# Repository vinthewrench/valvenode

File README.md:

# ValveNode

ValveNode is a wired field-bus irrigation valve-control system for my Raspberry Pi farm automation stack.

This project is a continuation of the work described in [Off-Grid Farm Automation with Raspberry Pi](https://www.vinthewrench.com/p/off-grid-farm-automation-raspberry-pi).

The irrigation side started with a Raspberry Pi, relay outputs, and conventional sprinkler valve wiring, described in [Raspberry Pi Internet of Things - part 2: Controlling the Irrigation valves](https://www.vinthewrench.com/p/raspberry-pi-internet-of-things-part-23c). That proved the basic idea: local software can control real irrigation hardware without a cloud service or proprietary controller. It also exposed the usual field problems: long wire runs, voltage drop, power loss, serviceability, and too many individual valve wires returning to one box.

I later experimented with more efficient solenoid drive hardware using a DRV103 in [Not Another Sprinkler Valve Article](https://www.vinthewrench.com/p/not-another-sprinkler-valve-article). That design gives a conventional valve a strong opening pulse and then reduces average power with PWM, which matters for long wire runs and battery-backed operation.

As the farm kept expanding, the wiring problem started to matter more than the valve-control problem. Every new irrigation zone meant another long wire run back to the controller, more trenching, more splices, more voltage drop, and more things to troubleshoot later. At that point, spending a few extra dollars per valve for latching solenoids was worth it if it let the field wiring become a simple 4-wire RS-485 network.

ValveNode takes the next step: instead of pulling every valve wire back to the controller, it moves small controller cards out into the field.

A Raspberry Pi talks to a Valve Master over I2C. The Valve Master starts a 4-wire RS-485 field cable carrying power and data. Valve Node cards sit along that cable, and each card drives a local latching irrigation solenoid with a short polarity-controlled pulse.

The goal is simple: irrigation control that is local, wired, understandable, repairable, and expandable.

## Overview

The project has two primary components:

- `valvenode-master`  
  ATmega88PB-based I2C-to-RS-485 master controller.

- `valvenode-slave`  
  ATtiny4313-based RS-485 valve node for controlling latching irrigation valves.

The upstream controller talks to the Valve Master over I2C. The Valve Master controls field power and communicates with downstream Valve Nodes over RS-485.

### Latching Solenoids

ValveNode is designed around low-voltage DC latching irrigation solenoids. The initial supported solenoids are:

| Manufacturer | Part | Description | Notes |
|---|---:|---|---|
| Hunter | [458200](https://www.hunterirrigation.com/irrigation-product/solenoids/458200) | DC latching solenoid | Common Hunter solenoid for battery-operated and DC-latching valve control |
| Rain Bird | [K80920](https://store.rainbird.com/tbospsol-tbos-potted-latching-solenoid.html) / TBOSPSOL | 9 V DC potted latching solenoid | Fits many Rain Bird valve bodies, including DV, DVF, ASVF, PGA, PEB, PESB, GB, EFB-CP, BPE, and BPES series valves |

A latching solenoid is not powered continuously. The Valve Node drives it with a short polarity-controlled pulse through the H-bridge: one polarity opens the valve, the opposite polarity closes it, and then the output is turned off.

## Project Goals

- Wired field-bus control for irrigation valves
- No cloud dependency
- No wireless dependency
- Local 12 V field-power switching
- Half-duplex RS-485 node communication
- AVR-based firmware that can be understood, built, and serviced
- KiCad hardware source included
- Separate master firmware, simulator, Linux test tool, and node firmware

## Repository Layout

~~~text
valvenode/
├── valvenode-master/
│   ├── docs/
│   ├── firmware/
│   ├── hw/
│   │   └── 1.0/
│   ├── sim/
│   └── test/
└── valvenode-slave/
    ├── docs/
    ├── firmware/
    ├── hw/
    │   ├── 1.0/
    │   └── 1.1/
    └── test/
~~~

## Valve Master

Path:

~~~text
valvenode-master/
~~~

The Valve Master is the central controller for the valve-node network.

It performs these jobs:

- Accepts host commands over I2C
- Controls switched 12 V field-bus power
- Sends RS-485 commands to downstream valve nodes
- Receives valve-node replies
- Maintains node discovery state
- Reports status and command results to the host
- Provides local visual status indication
- Exposes AVR ISP programming access

Default I2C address:

~~~text
0x09
~~~

Address `0x08` is reserved for a separate power-control board, so `0x09` is used as the default Valve Master address.

### Valve Master Hardware

Path:

~~~text
valvenode-master/hw/1.0/
~~~

Important KiCad source files:

~~~text
valvenode-master.kicad_pro
valvenode-master.kicad_sch
valvenode-master.kicad_pcb
~~~

The master board uses:

- ATmega88PB-AU
- MAX485-style RS-485 transceiver
- Relay-switched 12 V field-bus output
- FAULT input
- COMM and FAULT indicators
- AVR ISP header
- I2C host-side interface

### Valve Master Firmware

Path:

~~~text
valvenode-master/firmware/
~~~

Files:

~~~text
makefile
valvenode_master.c
~~~

The firmware implements the production Valve Master behavior:

- I2C slave interface
- Register map
- Deferred command handling
- RS-485 transmit/receive control
- Field-bus power control
- Node discovery
- Valve-node command dispatch
- Result and reply registers
- Fault/status reporting

Directed RS-485 commands include timeout handling and retry behavior. A single missed node reply should not turn into an immediate hard failure on a slow irrigation field bus.

Build:

~~~bash
cd valvenode-master/firmware
make
~~~

### Valve Master Simulator

Path:

~~~text
valvenode-master/sim/
~~~

Files:

~~~text
makefile
valvenode_master_sim.c
~~~

The simulator models the master command/register behavior for bench testing without hardware.

Build:

~~~bash
cd valvenode-master/sim
make
~~~

### Valve Master Linux Test Tool

Path:

~~~text
valvenode-master/test/
~~~

Files:

~~~text
makefile
Doxyfile
src/
~~~

Source files:

~~~text
I2C.cpp
I2C.hpp
LogMgr.cpp
LogMgr.hpp
TimeStamp.cpp
TimeStamp.hpp
Valve_master.cpp
Valve_master.hpp
main.cpp
~~~

The test tool is a Linux-side C++ program used to talk to the Valve Master over `/dev/i2c-*`.

The main C++ class is:

~~~text
Valve_master
~~~

It wraps the Valve Master I2C register map and command model.

Typical responsibilities:

- Open the Linux I2C device
- Select the Valve Master I2C address
- Read and write registers
- Submit commands
- Wait for command completion
- Read command results
- Read reply registers
- Read discovered node map
- Query firmware versions
- Control field power
- Ping nodes
- Set valve/channel state

Build:

~~~bash
cd valvenode-master/test
make
~~~

Common `valve` commands:

~~~bash
./valve status
./valve power on
./valve power off
./valve who
./valve map
./valve ping 1
./valve set 1 1 on
./valve set 1 1 off
./valve channel 1 1 status
./valve version master
./valve version 1
./valve identify 1
./valve cancel
~~~

Provisioning commands:

~~~bash
./valve config
./valve assign 7
./valve move 7 8
~~~

### Hammer Test

Path:

~~~text
valvenode-master/test/hammer.sh
~~~

`hammer.sh` repeatedly exercises the full Valve Master path.

Test pattern:

~~~text
power on
ping nodes
initial status nodes
loop:
  set ON nodes
  status nodes
  set OFF nodes
  status nodes
final status nodes
power off
~~~

Example:

~~~bash
cd valvenode-master/test
./hammer.sh 25
NODES="1 3 4 5 6" CHANNEL=1 ./hammer.sh 500
~~~

Optional settings:

~~~bash
CHANNEL=2 ./hammer.sh 25
VERBOSE=1 ./hammer.sh 25
VALVE_BIN=./valve ./hammer.sh 25
NODES="1 3 4 5 6" ./hammer.sh 25
RETRY_ON_FAIL=1 ./hammer.sh 25
~~~

Recent bench result:

~~~text
500 loops
5 nodes tested: 1 3 4 5 6
channel 1
10,016 commands
0 failures
100% first-try pass rate
~~~

Generate local Doxygen docs:

~~~bash
cd valvenode-master/test
doxygen Doxyfile
open docs/html/index.html
~~~

## Valve Master I2C Register Model

The host talks to the master through a small register map.

Important registers include:

~~~text
REG_COMMAND
REG_STATUS
REG_ARG0
REG_ARG1
REG_ARG2
REG_RESULT
REG_POWER_STATE
REG_NODE_COUNT
REG_REPLY_NODE
REG_REPLY_CMD
REG_REPLY_ARG0
REG_REPLY_ARG1
REG_VERSION_HI
REG_VERSION_LO
REG_NODE_MAP
~~~

Important command values include:

~~~text
CMD_POWER_ON
CMD_POWER_OFF
CMD_WHO
CMD_PING
CMD_SET_CHANNEL
CMD_GET_CHANNEL_STATUS
CMD_GET_NODE_VERSION
CMD_IDENTIFY
CMD_CANCEL
CMD_CONFIG
CMD_ASSIGN
CMD_CLEAR_ERROR
CMD_SET_ERROR
CMD_CLOSE_ALL
~~~

Important status bits include:

~~~text
STATUS_BUSY
STATUS_ERROR
STATUS_POWER_ON
~~~

Important result values include:

~~~text
RESULT_OK
RESULT_BAD_COMMAND
RESULT_BAD_NODE
RESULT_BAD_CHANNEL
RESULT_NODE_NOT_FOUND
RESULT_UNSUPPORTED_CHANNEL
RESULT_CONFIG_REQUIRED
RESULT_ADDRESS_IN_USE
RESULT_BUSY
RESULT_RS485_TIMEOUT
RESULT_RS485_BAD_CHECKSUM
RESULT_RS485_BAD_REPLY
RESULT_POWER_OFF
~~~

## Valve Node

Path:

~~~text
valvenode-slave/
~~~

The Valve Node is the remote field device. It receives RS-485 commands and drives a 12 V latching irrigation valve.

Core functions:

- Receive framed RS-485 commands
- Check destination address
- Respond to discovery and status commands
- Drive a latching valve using a polarity-controlled pulse
- Turn the H-bridge fully off after each pulse
- Report current logical valve state

### Valve Node Hardware

Paths:

~~~text
valvenode-slave/hw/1.0/
valvenode-slave/hw/1.1/
~~~

Important KiCad source files:

~~~text
valvenode.kicad_pro
valvenode.kicad_sch
valvenode.kicad_pcb
~~~

The `1.1` hardware directory is the newer active revision.

The node hardware uses:

- ATtiny4313
- 5 V RS-485 transceiver
- VNH7100BAS / VNH7100BASTR H-bridge
- 12 V latching irrigation valve output
- 12 V field-bus input
- Local 5 V regulator
- Optional status LED

Basic field connection:

~~~text
+12 V
GND
RS-485 A
RS-485 B
~~~

The design is intended for direct-burial irrigation cable.

Recommended cable:

- 18/4 acceptable for shorter runs
- 16/4 preferred for longer runs or higher node counts

### Valve Node Power Architecture

The node receives 12 V from the field cable.

Power paths:

- 12 V directly feeds the valve driver supply
- 12 V feeds a local 5 V regulator
- 5 V powers the ATtiny4313 and RS-485 transceiver

Recommended protection and stability parts include:

- Bidirectional TVS across the 12 V input
- Bulk capacitance near the H-bridge supply
- 0.1 uF local decoupling at MCU and transceiver
- Additional 5 V bulk capacitance near the MCU
- Reverse-polarity protection where practical

For master-side field power switching, allow roughly 250 to 300 ms after switching on the 12 V field bus before sending node commands.

### Valve Node Firmware

Path:

~~~text
valvenode-slave/firmware/
~~~

Files:

~~~text
makefile
valvenode.c
valvenode_example_commands.txt
~~~

The firmware target is the ATtiny4313.

Firmware responsibilities:

- UART receive
- RS-485 command parsing
- Address matching
- Optional checksum checking
- Valve open pulse
- Valve close pulse
- Status reporting
- Ping reply
- WHO discovery reply
- Safe H-bridge shutdown after each pulse

Build:

~~~bash
cd valvenode-slave/firmware
make
~~~

### Valve Node Test Tool

Path:

~~~text
valvenode-slave/test/
~~~

Files:

~~~text
makefile
src/main.cpp
~~~

The `vnode` utility is used for direct bench testing of valve nodes over a serial port. It assumes the computer is connected to the RS-485 bus through a USB-to-RS-485 adapter.

This bypasses the Valve Master and talks directly to the nodes.

Build:

~~~bash
cd valvenode-slave/test
make
~~~

Example:

~~~bash
./vnode -d /dev/ttyUSB0 who
./vnode -d /dev/ttyUSB0 ping 1
./vnode -d /dev/ttyUSB0 open 1 1
./vnode -d /dev/ttyUSB0 close 1 1
~~~

Typical output:

~~~text
$ ./vnode -d /dev/ttyUSB0 who
device: /dev/ttyUSB0
baud:   9600
tx: :FFW\r
rx: :01WB8  [checksum ok] node=1 WHO
rx: :02WB9  [checksum ok] node=2 WHO
~~~

`vnode` can also be used to configure a fresh node, assign its address, and verify that it answers before it goes into the field.

## RS-485 Valve Node Protocol

The Valve Master and Valve Nodes communicate over a half-duplex RS-485 bus.

The node protocol is command/response. The master sends a framed command. A node replies only when addressed or when participating in a controlled discovery response.

Typical commands:

~~~text
PING
STATUS
OPEN
CLOSE
WHO
IDENTIFY
CONFIG
ASSIGN
VERSION
~~~

Typical behavior:

- `PING` confirms node presence
- `STATUS` reports logical valve/channel state
- `OPEN` sends the open-polarity valve pulse
- `CLOSE` sends the close-polarity valve pulse
- `WHO` is used for node discovery
- `IDENTIFY` asks a node to identify itself
- `CONFIG` enters configuration behavior
- `ASSIGN` sets or changes a node address
- `VERSION` reports firmware version

Broadcast state-changing commands should be avoided unless explicitly implemented and safe.

## Useful Linux I2C Commands

List I2C buses:

~~~bash
i2cdetect -l
ls -l /dev/i2c-*
~~~

Scan I2C bus 1:

~~~bash
i2cdetect -y 1
~~~

Look for the Valve Master at address `0x09`.

Check user permissions for I2C:

~~~bash
groups
ls -l /dev/i2c-*
~~~

If needed, add the user to the `i2c` group on Linux:

~~~bash
sudo usermod -aG i2c $USER
~~~

Then log out and back in.

## Development Notes

- The Valve Master default I2C address is `0x09`.
- The Valve Master controls field-bus 12 V power.
- The Valve Nodes are not autonomous irrigation controllers.
- Valve Nodes execute direct command/response behavior.
- Latching valves must be driven with short pulses, not continuous power.
- H-bridge outputs must be turned off after each pulse.
- RS-485 bus direction control must be handled carefully to avoid bus contention.
- Field wiring should assume noise, voltage drop, wet boxes, lightning exposure, and field-service abuse.

## Current Project Status

The repository currently contains:

- Valve Master hardware design
- Valve Master firmware
- Valve Master simulator
- Valve Master Linux I2C test tool: `valve`
- Valve Master hammer test: `hammer.sh`
- Valve Node hardware revisions
- Valve Node firmware
- Valve Node direct RS-485 test tool: `vnode`
- Protocol and design documentation

Current bench status:

- Valve Master can switch field power
- Valve Master can communicate with multiple valve nodes over RS-485
- Valve nodes respond to discovery, ping, set, and status commands
- `hammer.sh` has completed a 500-loop, 10,016-command bench test across five nodes with zero failures

Remaining validation:

- Confirm final latching-solenoid open/close polarity with real valve bodies
- Test final assembled boards in outdoor enclosures
- Validate longer real field-cable runs
- Continue field reliability testing before treating the system as deployed infrastructure

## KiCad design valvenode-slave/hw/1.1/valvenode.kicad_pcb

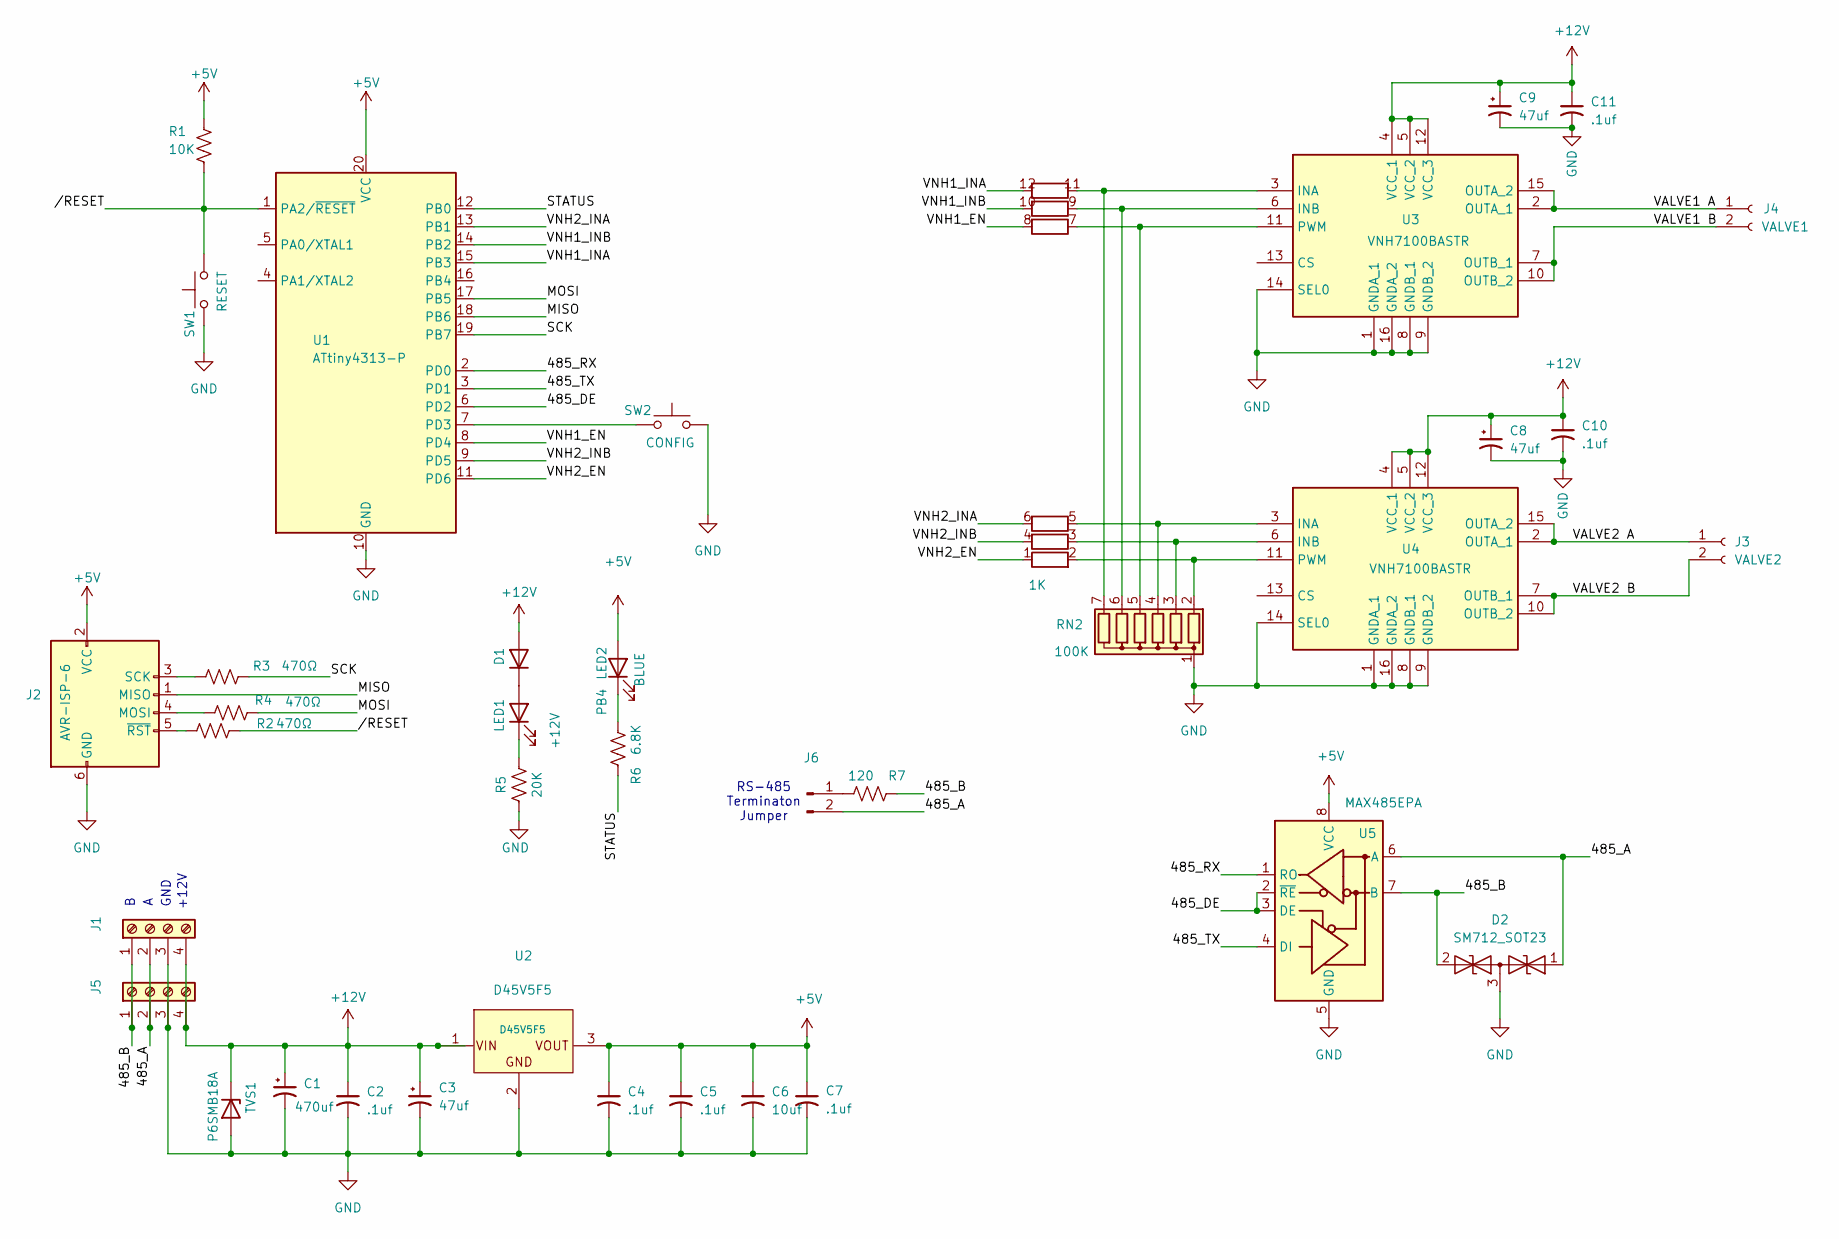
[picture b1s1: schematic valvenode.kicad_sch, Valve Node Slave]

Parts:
C1: 470uf; CP_Radial_D5.0mm_P2.00mm
C2, C4, C5, C7, C10, C11: .1uf; RCER71H104K0DBH03A
C3, C8, C9: 47uf; CP_Radial_D5.0mm_P2.00mm
C6: 10uf; CP_Radial_D5.0mm_P2.00mm
D1: 1N4148WS; D_DO-35_SOD27_P7.62mm_Horizontal
D2: SM712_SOT23; SOT-23
J1, J5: +12; TerminalBlock_Phoenix_MKDS-1,5-4-5.08_1x04_P5.08mm_Horizont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
J2: AVR-ISP-6; PinHeader_2x03_P2.54mm_Vertical
J3: VALVE2; TerminalBlock_Phoenix_MKDS-1,5-2-5.08_1x02_P5.08mm_Horizont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
J4: VALVE1; TerminalBlock_Phoenix_MKDS-1,5-2-5.08_1x02_P5.08mm_Horizont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
J6: Conn_01x02_Pin; PinHeader_1x02_P2.54mm_Vertical
LED1: 151033GS03000; LED_D3.0mm
LED2: 1510x4BS03000; LED_D3.0mm
R1: 10K; R_Axial_DIN0204_L3.6mm_D1.6mm_P7.62mm_Horizontal
R2, R3, R4: 470Ω; R_Axial_DIN0204_L3.6mm_D1.6mm_P7.62mm_Horizontal
R5: 20K; R_Axial_DIN0204_L3.6mm_D1.6mm_P7.62mm_Horizontal
R6: 6.8K; R_Axial_DIN0204_L3.6mm_D1.6mm_P7.62mm_Horizontal
R7: 120; R_Axial_DIN0204_L3.6mm_D1.6mm_P7.62mm_Horizontal
RN1: 1K; R_Array_SIP12; Manufacturer_Part_Number 4612X-102-102LF
RN2: 100K; R_Array_SIP7; Manufacturer_Part_Number 4607X-101-104LF
SW1: RESET; SW_PUSH_6mm
SW2: CONFIG; SW_PUSH_6mm
TVS1: P6SMB18A; D_SMB_Handsoldering
U1: ATtiny4313-P; DIP-20_W7.62mm
U2: D45V5F5
U3, U4: VNH7100BASTR; SOIC127P600X175-16N; Manufacturer_Part_Number VNH7100BASTR; Mouser Part Number 511-VNH7100BASTR
U5: MAX485EPA; DIP-8_W7.62mm

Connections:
+5V: C4.1, C5.1, C6.1, C7.1, J2.2 (VCC), LED2.2 (A), R1.1, U1.20 (VCC), U2.3 (VOUT), U5.8 (VCC)
+12V: C1.1, C2.1, C3.1, C8.1, C9.1, C10.1, C11.1, D1.2 (A), J1.4, J5.4, TVS1.1 (K), U2.1 (VIN), U3.4 (VCC_1), U3.5 (VCC_2), U3.12 (VCC_3), U4.4 (VCC_1), U4.5 (VCC_2), U4.12 (VCC_3)
/485_A: D2.1 (A1), J1.2, J5.2, J6.2, U5.6 (A)
/485_B: D2.2 (A2), J1.1, J5.1, R7.1, U5.7 (B)
/485_DE: U1.6 (PD2), U5.2 (~RE), U5.3 (DE)
/485_RX: U1.2 (PD0), U5.1 (RO)
/485_TX: U1.3 (PD1), U5.4 (DI)
/MISO: J2.1 (MISO), U1.18 (PB6)
/MOSI: R4.1, U1.17 (PB5)
/SCK: R3.1, U1.19 (PB7)
/STATUS: R6.1, U1.12 (PB0)
/VALVE1 A: J4.1, U3.2 (OUTA_1), U3.15 (OUTA_2)
/VALVE1 B: J4.2, U3.7 (OUTB_1), U3.10 (OUTB_2)
/VALVE2 A: J3.1, U4.2 (OUTA_1), U4.15 (OUTA_2)
/VALVE2 B: J3.2, U4.7 (OUTB_1), U4.10 (OUTB_2)
/VNH1_EN: RN1.8 (R4.2), U1.8 (PD4)
/VNH1_INA: RN1.12 (R6.2), U1.15 (PB3)
/VNH1_INB: RN1.10 (R5.2), U1.14 (PB2)
/VNH2_EN: RN1.1 (R1.1), U1.11 (PD6)
/VNH2_INA: RN1.6 (R3.2), U1.13 (PB1)
/VNH2_INB: RN1.4 (R2.2), U1.9 (PD5)
//RESET: R1.2, R2.1, SW1.2, U1.1 (PA2/~RESET)
GND: C1.2, C2.2, C3.2, C4.2, C5.2, C6.2, C7.2, C8.2, C9.2, C10.2, C11.2, D2.3 (common), J1.3, J2.6 (GND), J5.3, R5.2, RN2.1 (common), SW1.1, SW2.2, TVS1.2 (A), U1.10 (GND), U2.2 (GND), U3.1 (GNDA_1), U3.8 (GNDB_1), U3.9 (GNDB_2), U3.14 (SEL0), U3.16 (GNDA_2), U4.1 (GNDA_1), U4.8 (GNDB_1), U4.9 (GNDB_2), U4.14 (SEL0), U4.16 (GNDA_2), U5.5 (GND)
unnamed: D1.1 (K), LED1.2 (A)
unnamed: J2.4 (MOSI), R4.2
unnamed: J2.3 (SCK), R3.2
unnamed: J2.5 (~RST), R2.2
unnamed: J6.1, R7.2
unnamed: LED1.1 (K), R5.1
unnamed: LED2.1 (K), R6.2
unnamed: RN1.2 (R1.2), RN2.2 (R1), U4.11 (PWM)
unnamed: RN1.3 (R2.1), RN2.3 (R2), U4.6 (INB)
unnamed: RN1.5 (R3.1), RN2.4 (R3), U4.3 (INA)
unnamed: RN1.7 (R4.1), RN2.5 (R4), U3.11 (PWM)
unnamed: RN1.9 (R5.1), RN2.6 (R5), U3.6 (INB)
unnamed: RN1.11 (R6.1), RN2.7 (R6), U3.3 (INA)
unnamed: SW2.1, U1.7 (PD3)

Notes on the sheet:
RS-485 Terminaton Jumper
GND
+12V

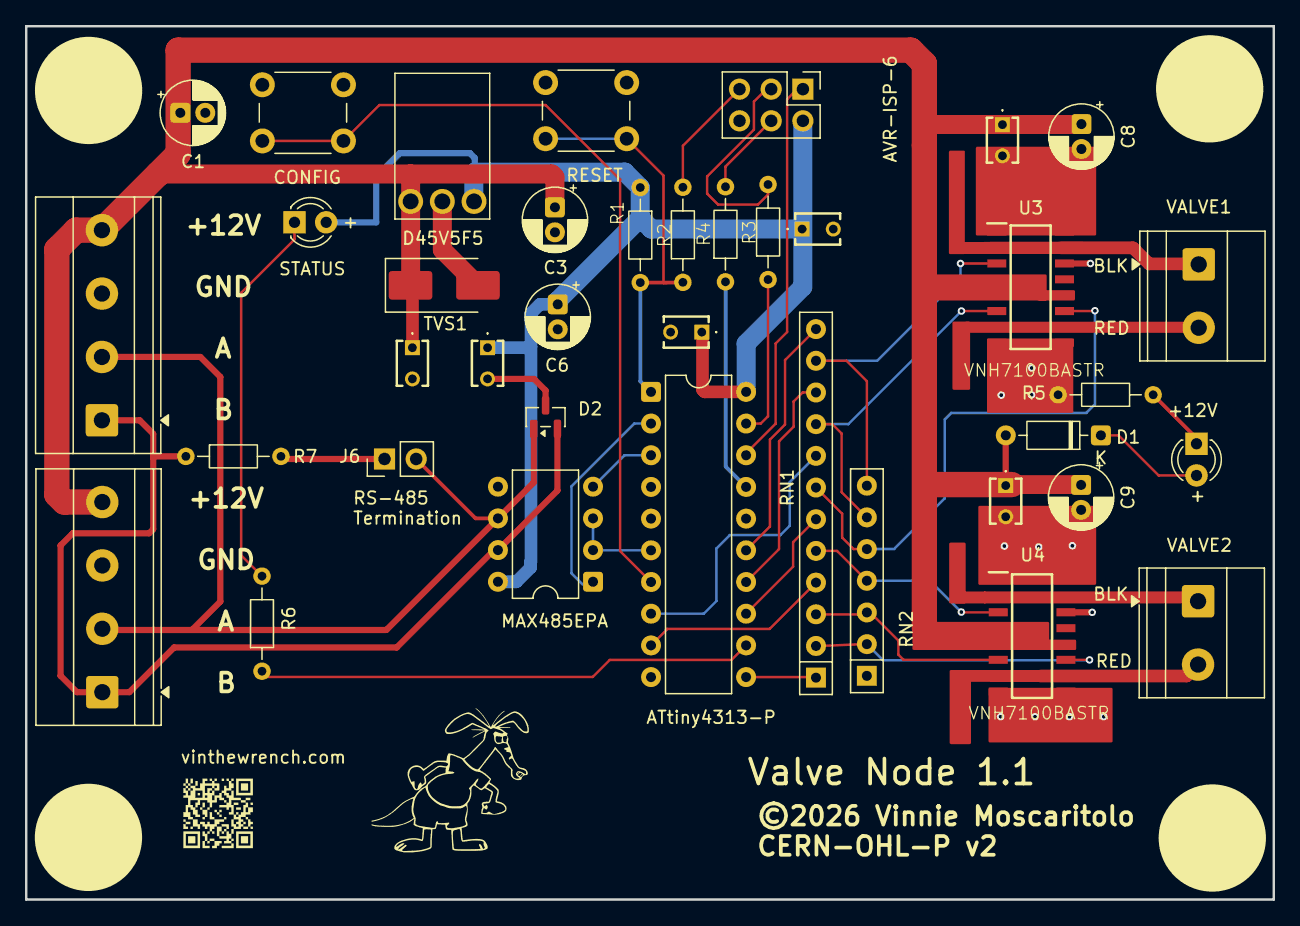
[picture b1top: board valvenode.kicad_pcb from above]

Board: 2 copper layers, 100.0 x 70.0 mm, 39 parts (0 on the bottom side), 37 nets.

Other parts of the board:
X: LOGO; aard1

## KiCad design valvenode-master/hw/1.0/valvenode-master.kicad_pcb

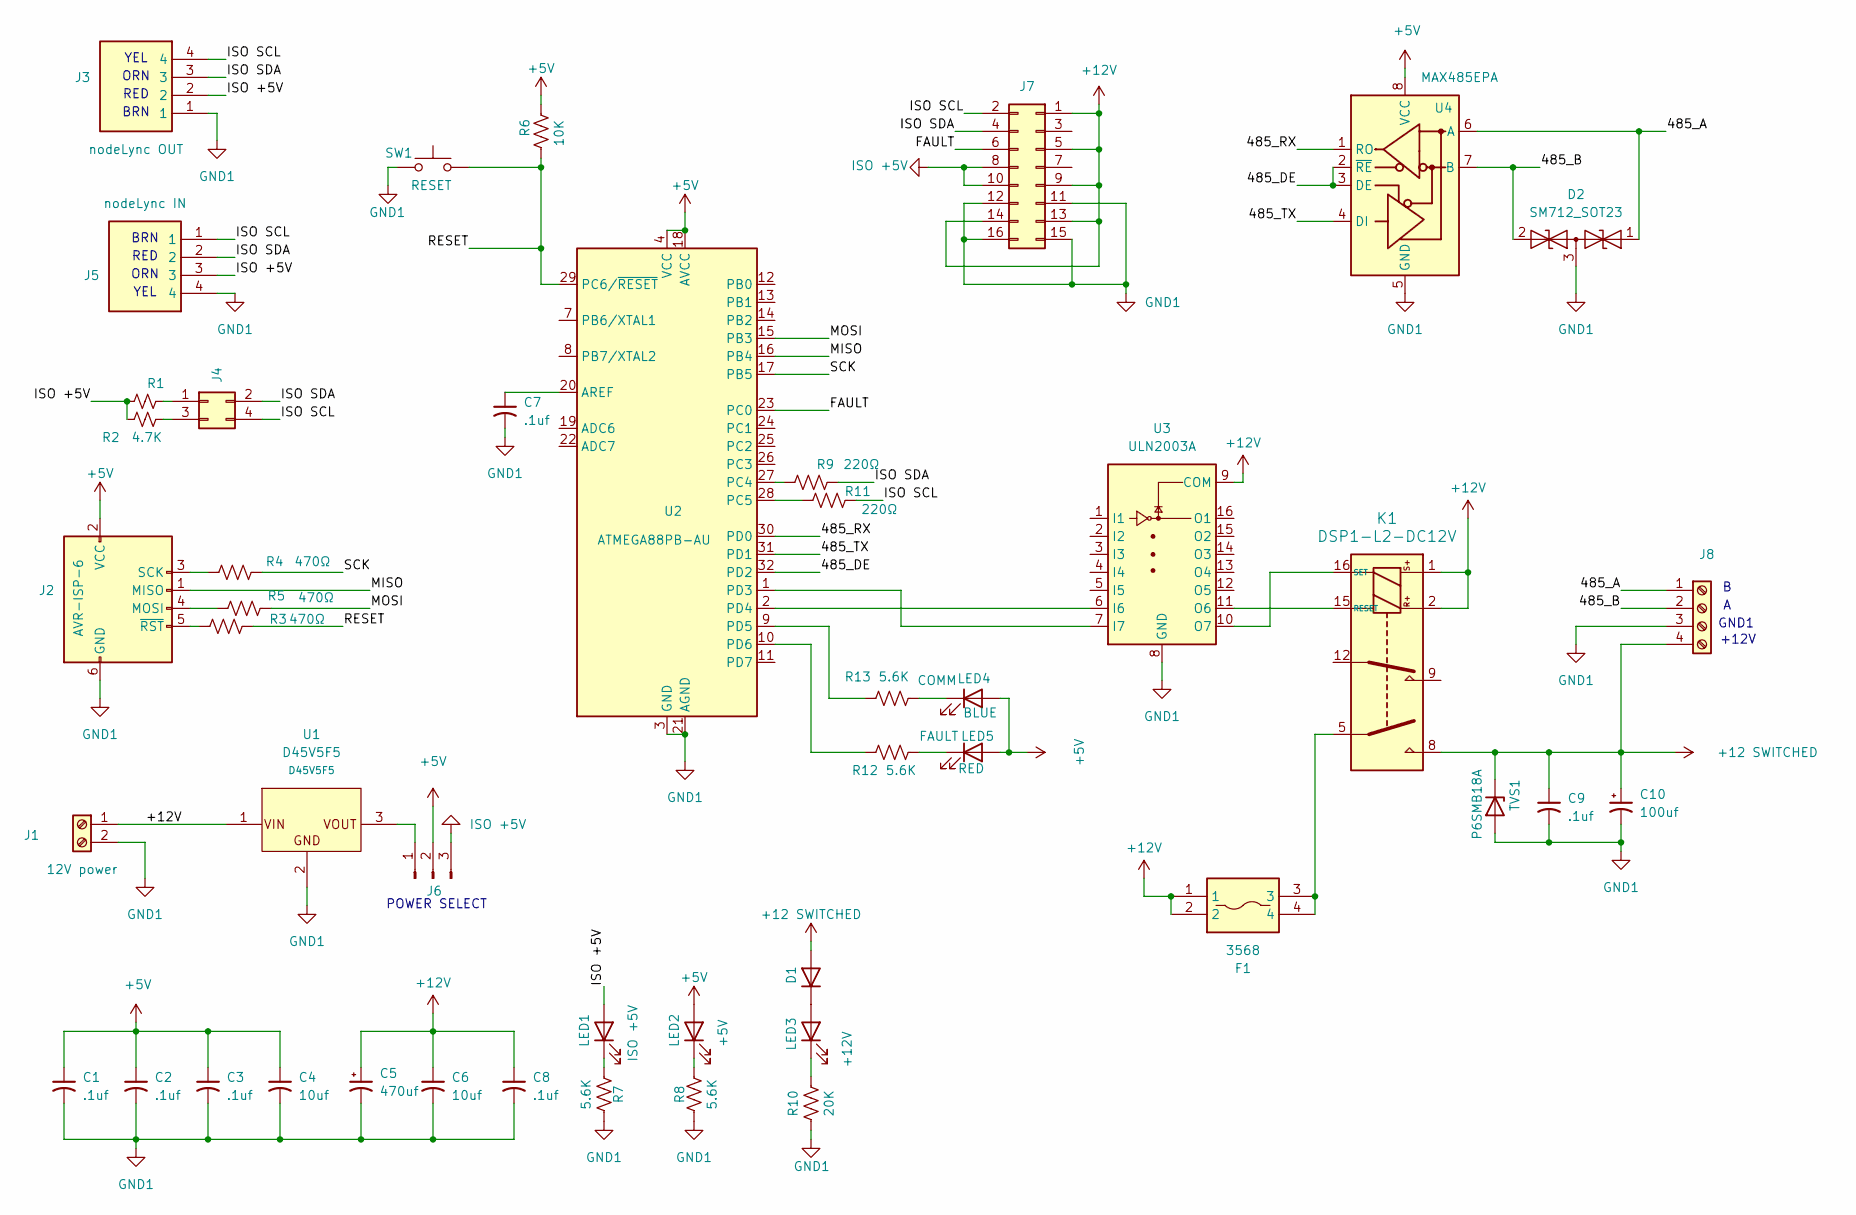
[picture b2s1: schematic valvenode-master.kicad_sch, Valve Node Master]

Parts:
C1, C2, C3, C7, C8, C9: .1uf; RCER71H104K0DBH03A
C4, C6: 10uf; CP_Radial_D5.0mm_P2.00mm
C5: 470uf; CP_Radial_D8.0mm_P3.50mm
C10: 100uf; CP_Radial_D8.0mm_P3.50mm
D1: 1N4148WS; D_DO-35_SOD27_P7.62mm_Horizontal
D2: SM712_SOT23; SOT-23
F1: 3568; Mouser Part Number 534-3568
J1: 12V power; TerminalBlock_Phoenix_MKDS-1,5-2-5.08_1x02_P5.08mm_Horizont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
J2: AVR-ISP-6; PinHeader_2x03_P2.54mm_Vertical
J3, J5: 70551-0003; 705510003; Manufacturer_Part_Number 70551-0003; Mouser Part Number 538-70551-0003
J4: Conn_02x02_Odd_Even; PinHeader_2x02_P2.54mm_Vertical
J6: Conn_01x03_Pin; PinHeader_1x03_P2.54mm_Vertical
J7: Conn_02x08_Odd_Even; PinSocket_2x08_P2.54mm_Vertical
J8: +12; TerminalBlock_Phoenix_MKDS-1,5-4-5.08_1x04_P5.08mm_Horizont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
K1: DSP1-L2-DC12V
LED1, LED2, LED3: 151033GS03000; LED_D3.0mm
LED4: 151034BS03000; LED_D3.0mm
LED5: 151033RS03000; LED_D3.0mm
R1, R2: 4.7K; R_Axial_DIN0204_L3.6mm_D1.6mm_P7.62mm_Horizontal
R3, R4, R5: 470Ω; R_Axial_DIN0204_L3.6mm_D1.6mm_P7.62mm_Horizontal
R6: 10K; R_Axial_DIN0204_L3.6mm_D1.6mm_P7.62mm_Horizontal
R7, R8, R12, R13: 5.6K; R_Axial_DIN0204_L3.6mm_D1.6mm_P7.62mm_Horizontal
R9, R11: 220Ω; R_Axial_DIN0204_L3.6mm_D1.6mm_P7.62mm_Horizontal
R10: 20K; R_Axial_DIN0204_L3.6mm_D1.6mm_P7.62mm_Horizontal
SW1: RESET; SW_PUSH_6mm
TVS1: P6SMB18A; D_SMB_Handsoldering
U1: D45V5F5
U2: ATMEGA88PB-AU; TQFP-32_7x7mm_P0.8mm
U3: ULN2003A; DIP-16_W7.62mm
U4: MAX485EPA; DIP-8_W7.62mm

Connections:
+5V: C1.1, C2.1, C3.1, C4.1, J2.2 (VCC), J6.2, LED2.2 (A), LED4.2 (A), LED5.2 (A), R6.1, U2.4 (VCC), U2.6 (VCC), U2.18 (AVCC), U4.8 (VCC); also elsewhere on the board
+12 SWITCHED: C9.1, C10.1, D1.2 (A), J8.4, K1.8, TVS1.1 (K)
+12V: C5.1, C6.1, C8.1, F1.1, F1.2, J1.1, J7.1, J7.5, J7.9, J7.13, J7.14, K1.1, K1.2, U1.1 (VIN), U3.9 (COM); also elsewhere on the board
/485_A: D2.1 (A1), J8.1, U4.6 (A)
/485_B: D2.2 (A2), J8.2, U4.7 (B)
/485_DE: U2.32 (PD2), U4.2 (~RE), U4.3 (DE)
/485_RX: U2.30 (PD0), U4.1 (RO)
/485_TX: U2.31 (PD1), U4.4 (DI)
/FAULT: J7.6, U2.23 (PC0)
/ISO SCL: J3.4, J4.4, J5.1, J7.2, R11.1
/ISO SDA: J3.3, J4.2, J5.2, J7.4, R9.1
/MISO: J2.1 (MISO), U2.16 (PB4)
/MOSI: R5.1, U2.15 (PB3)
/RESET: R3.1, R6.2, SW1.2, U2.29 (PC6/~RESET)
/SCK: R4.1, U2.17 (PB5)
GND1: C1.2, C2.2, C3.2, C4.2, C5.2, C6.2, C7.2, C8.2, C9.2, C10.2, D2.3 (common), J1.2, J2.6 (GND), J3.1, J5.4, J7.11, J7.12, J7.15, J7.16, J8.3, R7.2, R8.1, R10.2, SW1.1, TVS1.2 (A), U1.2 (GND), U2.3 (GND), U2.5 (GND), U2.21 (AGND), U3.8 (GND), U4.5 (GND)
ISO +5V: J3.2, J5.3, J6.3, J7.8, J7.10, LED1.2 (A), R1.2, R2.2
unnamed: D1.1 (K), LED3.2 (A)
unnamed 18: F1.3, F1.4, K1.5; also elsewhere on the board
unnamed: J2.4 (MOSI), R5.2
unnamed: J2.3 (SCK), R4.2
unnamed: J2.5 (~RST), R3.2
unnamed: J4.1, R1.1
unnamed: J4.3, R2.1
unnamed: J6.1, U1.3 (VOUT)
unnamed: K1.15 (RESET), U3.11 (O6)
unnamed: K1.16 (SET), U3.10 (O7)
unnamed: LED1.1 (K), R7.1
unnamed: LED2.1 (K), R8.2
unnamed: LED3.1 (K), R10.1
unnamed 30: LED4.1 (K), R13.2; also elsewhere on the board
unnamed 31: LED5.1 (K), R12.2; also elsewhere on the board
unnamed: C7.1, U2.20 (AREF)
unnamed: R9.2, U2.27 (PC4)
unnamed: R11.2, U2.28 (PC5)
unnamed: U2.1 (PD3), U3.7 (I7)
unnamed: U2.2 (PD4), U3.6 (I6)
unnamed: R13.1, U2.9 (PD5)
unnamed: R12.1, U2.10 (PD6)

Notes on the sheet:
GND1
YEL
BRN
ORN
+12V
POWER SELECT
RED

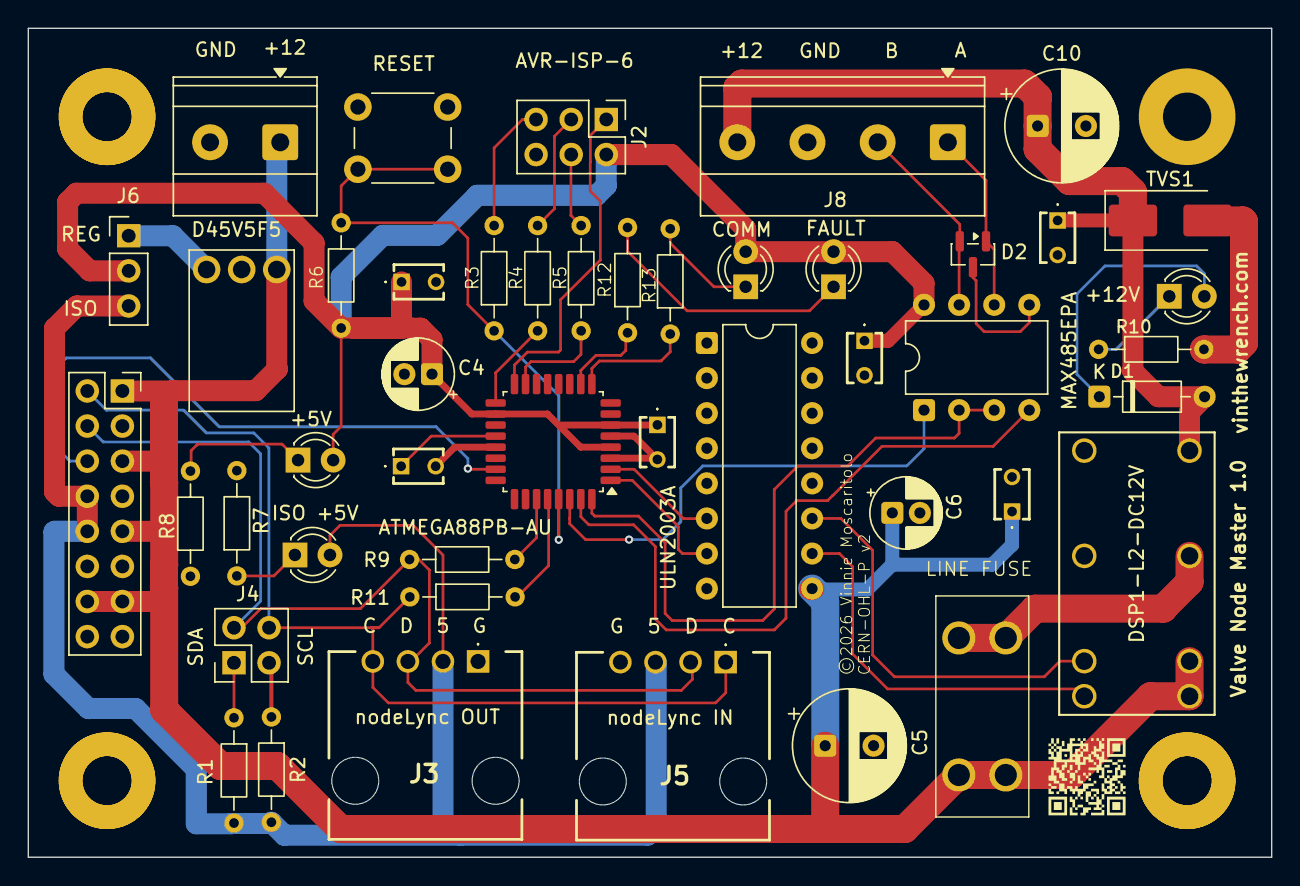
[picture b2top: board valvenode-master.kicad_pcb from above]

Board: 2 copper layers, 90.0 x 60.0 mm, 50 parts (0 on the bottom side), 39 nets.

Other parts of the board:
COMM: 151034BS03000; LED_D3.0mm
FAULT: 151033RS03000; LED_D3.0mm
H1, H2, H3, H4: MountingHole_3.5mm_Pad
LINE FUSE: 3568

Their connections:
+5V: COMM.2 (A), FAULT.2 (A); also elsewhere on the board
+12V: LINE FUSE.1, LINE FUSE.2; also elsewhere on the board
unnamed 18: LINE FUSE.3, LINE FUSE.4; also elsewhere on the board
unnamed 30: COMM.1 (K); also elsewhere on the board
unnamed 31: FAULT.1 (K); also elsewhere on the board

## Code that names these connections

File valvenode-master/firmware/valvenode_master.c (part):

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 * Request checksums are now always sent. Reply checksums are verified.
 *
 * Locked product MCU pin assignments:
 *   PB3  MOSI
 *   PB4  MISO
 *   PB5  SCK
 *   PC0  FAULT_OUT, open-drain style: normal = high-Z, fault = driven low
 *   PC4  SDA
 *   PC5  SCL
 *   PD0  485RX
 *   PD1  485TX
 *   PD2  485DE
 *   PD3  RELAY_SET
 *   PD4  RELAY_RESET
 *   PD5  BLUE_LED_COMM
 *   PD6  RED_LED_FAULT
 */

#ifndef F_CPU
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 * Product hardware pin map
 * ========================================================================== */

#define FAULT_OUT_PIN               PC0
#define RS485_DE_PIN                PD2
#define RELAY_SET_PIN               PD3
#define RELAY_RESET_PIN             PD4
#define COMM_LED_PIN                PD5
#define FAULT_LED_PIN               PD6

/* ============================================================================
 * Timing
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
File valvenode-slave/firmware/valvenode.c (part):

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 *   - 00     invalid / unassigned address
 *
 * Correct checksummed request examples:
 *   - :04PB4   ping node 04
 *   - :04O1E4  open valve 1 on node 04
 *   - :04C1D8  close valve 1 on node 04
 *   - :04O2E5  open valve 2 on node 04
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 *   ':' and EOL are not included in the checksum.
 *
 * Behavioral notes:
 *   - Active-low status LED on PB0
 *   - RS-485 DE and /RE are tied together on PD2
 *   - Replies always include checksum
 *   - Requests require checksum by default
 *   - Checksumless requests are allowed only if REQUIRE_RX_CHECKSUM is disabled
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 */
#define RS485_DIR_PORT                 PORTD
#define RS485_DIR_DDR                  DDRD
#define RS485_DIR_BIT                  PD2
/** @} */

/** @name Valve 1 driver pins
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 */
#define VNH1_PORT                      PORTB
#define VNH1_DDR                       DDRB
#define VNH1_INA_BIT                   PB3
#define VNH1_INB_BIT                   PB2
#define VNH1_PWM_PORT                  PORTD
#define VNH1_PWM_DDR                   DDRD
#define VNH1_PWM_BIT                   PD4
/** @} */

/** @name Valve 2 driver pins
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 */
#define VNH2_PORT                      PORTB
#define VNH2_DDR                       DDRB
#define VNH2_INA_BIT                   PB1
#define VNH2_INB_PORT                  PORTD
#define VNH2_INB_DDR                   DDRD
#define VNH2_INB_BIT                   PD5
#define VNH2_PWM_PORT                  PORTD
#define VNH2_PWM_DDR                   DDRD
#define VNH2_PWM_BIT                   PD6
/** @} */

/** @name Status LED
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 */
#define LED_PORT                       PORTB
#define LED_DDR                        DDRB
#define LED_BIT                        PB0
/** @} */

/** @name Config button input
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#define CONFIG_BTN_PORT                PORTD
#define CONFIG_BTN_DDR                 DDRD
#define CONFIG_BTN_PINR                PIND
#define CONFIG_BTN_BIT                 PD3
/** @} */

/* ============================================================================
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
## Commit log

2026-05-03 Initial valvenode project import
2026-05-03 Add ValveNode design documentation
2026-05-03 Add software and hardware licenses
2026-05-10 Add broadcast close-all command path
2026-05-10 Add close-all, RS-485 delay, and valve polarity fix
2026-05-10 Add protocol diagram
2026-05-10 fixup
2026-05-11 Update ValveNode master reliability and test tools
2026-05-18 Fix ValveNode EEPROM identity and test scripts
2026-05-22 Add VALVEMASTER piotserver driver and document valve node firmware
2026-05-23 Sync ValveNode master and slave firmware
2026-05-23 Fix ValveMaster diagnostics, harness checks, and slave EFUSE
2026-05-24 Add Valve Master action thread verification and harness tests
2026-05-25 Stabilize VALVEMASTER driver and test harness
2026-06-08 Harden Valve Master I2C handling
2026-06-12 Add ValveNode RS-485 sniffer

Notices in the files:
valvenode-master/hw/1.0/valvenode-master.kicad_pcb:
©2026 Vinnie Moscaritolo
CERN-OHL-P v2
valvenode-master/hw/1.0/valvenode-master.kicad_sch:
CERN-OHL-P v2 Permissive Open Hardware Licence
